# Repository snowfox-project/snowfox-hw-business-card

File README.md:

# Snowfox HW Business Card

## PCB

### Top

### Bottom

## Microcontroller

### pin usage

| pin | signal | direction | comment |
|-----|----------|-------------|--------------|
| gpio_0 | LED | output | user led |
| gpio_1 | GPIO_1 | undefined | |
| gpio_2 | SPI_CS_SD | output | chip select SD card |
| gpio_3 | SPI_MOSI | output | |
| gpio_4 | SPI_MISO | input | |
| gpio_5 | SPI_CLK | output | |
| gpio_9 | SPI_CS_DIS | output | chip selecet display |
| gpio_10 | DIS_RESET# | output | display reset |
| gpio_11 | DIS_D_C# | output | display data/command |
| gpio_12 | I2C_SDA | bidir | I2C data |
| gpio_13 | I2C_SCL | output | I2C clock |
| gpio_16 | RX | input | serial rx to USB |
| gpio_17 | TX | output | serial tx to USB |
| gpio_18 | EXT_TX | output | serial tx to expansion connector |
| gpio_19 | DIS_BUSY | input | display busy |
| gpio_20 | NFC_BUSY | input | nfc busy |
| gpio_21 | BUTTON_A | input | button left |
| gpio_22 | BUTTON_B | input | button right |
| gpio_23 | EXT_RX | input | serial rx to expansion connector |

### i2c addresses

| address | device | comment |
|-----|----------|--------------|
| 0x18 | BMA253 | accelerometer |
| 0x53 | M24LR | NFC eeprom - memory area |
| 0x57 | M24LR | NFC eeprom - security and data area |
| 0x60 | ATECC608A | crypto device |

The M24LR blocks two I2C adresses.

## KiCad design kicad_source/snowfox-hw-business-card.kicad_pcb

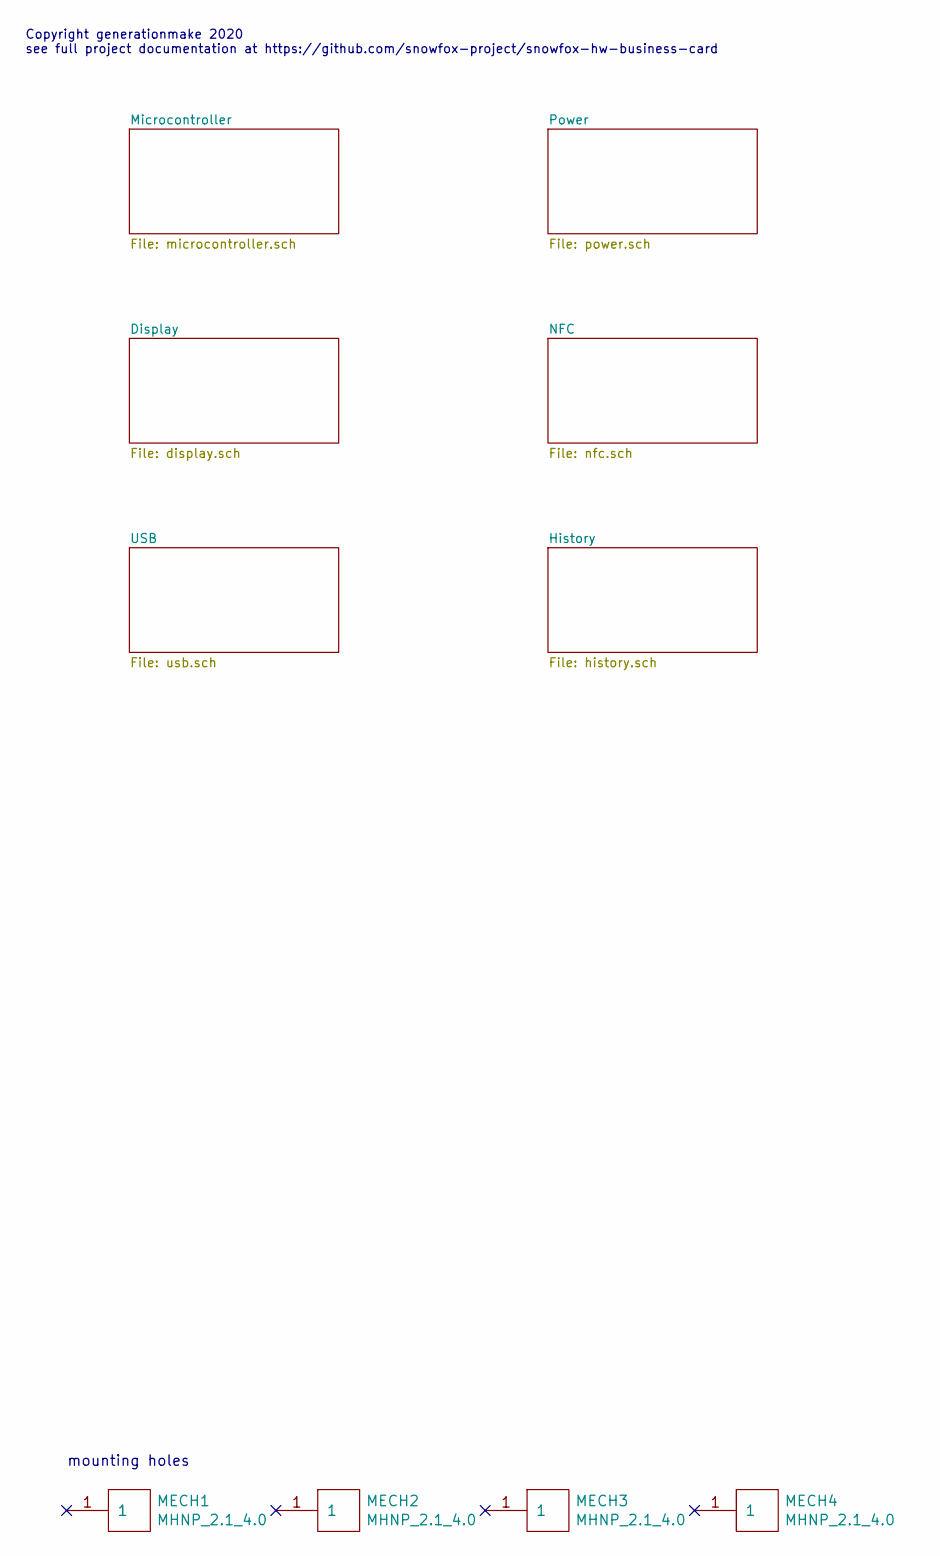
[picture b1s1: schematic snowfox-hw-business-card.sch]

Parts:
MECH1, MECH2, MECH3, MECH4: MHNP_2.1_4.0; MH_210_400_NP

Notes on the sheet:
mounting holes
Copyright generationmake 2020 see full project documentation at https://github.com/snowfox-project/snowfox-hw-business-card

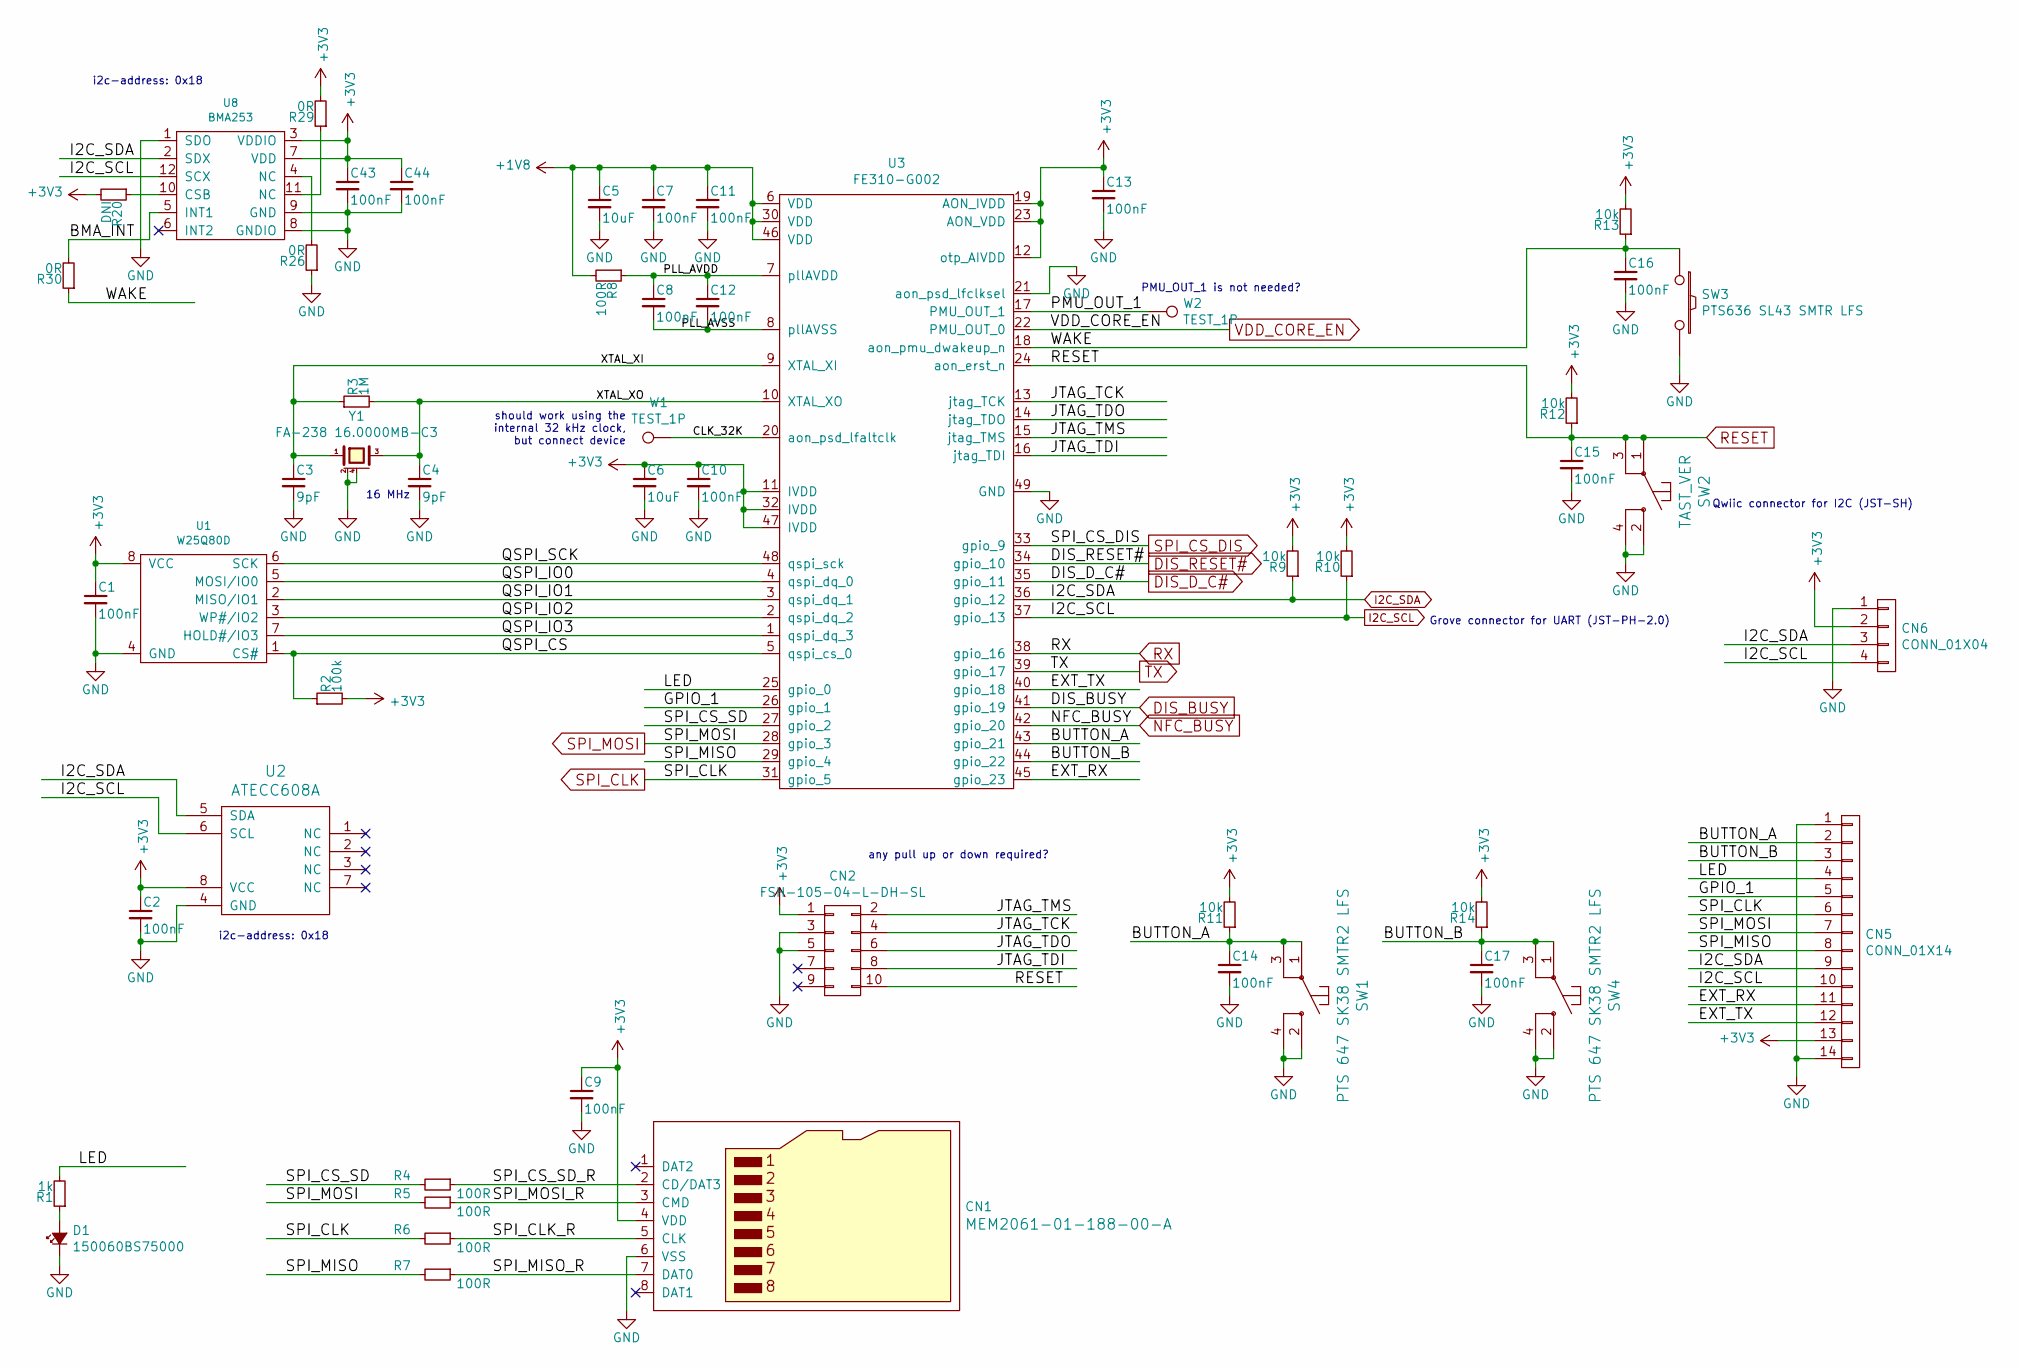
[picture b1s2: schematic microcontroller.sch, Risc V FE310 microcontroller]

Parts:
C1, C2, C7, C8, C9, C10, C11, C12, C13, C14, C15, C16, C17, C43, C44: 100nF; C_0603
C3, C4: 9pF; C_0603
C5, C6: 10uF; C_0603
CN1: MEM2061-01-188-00-A; WE_693071010811
CN2: FSH-105-04-L-DH-SL
CN5: CONN_01X14; SIB-114-02-F-S_MATING
CN6: CONN_01X04; Connectors_JST_SM04B-SRSS-TB
D1: 150060BS75000; LED_0603
R1: 1k; R_0603
R2: 100k; R_0603
R3: 1M; R_0603
R4, R5, R6, R7, R8: 100R; R_0603
R9, R10, R11, R12, R13, R14: 10k; R_0603
R20: DNI; R_0603
R26, R29, R30: 0R; R_0603
SW1, SW4: PTS 647 SK38 SMTR2 LFS; CK_PTS647
SW2: TAST_VER; WE_434351045816
SW3: PTS636 SL43 SMTR LFS; WE_434121050816
U1: W25Q80D; SOIC-8_3.9x4.9mm_Pitch1.27mm
U2: ATECC608A; SOIC-8_3.9x4.9mm_Pitch1.27mm
U3: FE310-G002; QFN-48-1EP_6x6mm_P0.4mm_EP4.3x4.3mm
U8: BMA253; BMA400
W1, W2: TEST_1P; SolderWirePad_single_1mmSMD
Y1: FA-238 16.0000MB-C3; Crystal_SMD_3.2x2.5mm_4Pad

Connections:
+1V8: C5.1, C7.1, C11.1, R8.2, U3.6 (VDD), U3.30 (VDD), U3.46 (VDD); also elsewhere on the board
+3V3: C1.1, C2.1, C6.1, C9.1, C10.1, C13.1, C43.1, C44.1, CN1.4 (VDD), CN2.1, CN5.13, CN6.2, R2.2, R9.2, R10.2, R11.2, R12.2, R13.2, R14.2, R20.2, R29.2, U1.8 (VCC), U2.8 (VCC), U3.11 (IVDD), U3.12 (otp_AIVDD), U3.19 (AON_IVDD), U3.23 (AON_VDD), U3.32 (IVDD), U3.47 (IVDD), U8.3 (VDDIO), U8.7 (VDD); also elsewhere on the board
/Microcontroller/BMA_INT: R30.2, U8.5 (INT1)
/Microcontroller/BUTTON_A: C14.1, CN5.2, R11.1, SW1.1, SW1.3, U3.43 (gpio_21)
/Microcontroller/BUTTON_B: C17.1, CN5.3, R14.1, SW4.1, SW4.3, U3.44 (gpio_22)
/Microcontroller/CLK_32K: U3.20 (aon_psd_lfaltclk), W1.1
/Microcontroller/EXT_RX: CN5.11, U3.45 (gpio_23)
/Microcontroller/EXT_TX: CN5.12, U3.40 (gpio_18)
/Microcontroller/GPIO_1: CN5.5, U3.26 (gpio_1)
/Microcontroller/JTAG_TCK: CN2.4, U3.13 (jtag_TCK)
/Microcontroller/JTAG_TDI: CN2.8, U3.16 (jtag_TDI)
/Microcontroller/JTAG_TDO: CN2.6, U3.14 (jtag_TDO)
/Microcontroller/JTAG_TMS: CN2.2, U3.15 (jtag_TMS)
/Microcontroller/LED: CN5.4, R1.2, U3.25 (gpio_0)
/Microcontroller/PLL_AVDD: C8.1, C12.1, R8.1, U3.7 (pllAVDD)
/Microcontroller/PLL_AVSS: C8.2, C12.2, U3.8 (pllAVSS)
/Microcontroller/PMU_OUT_1: U3.17 (PMU_OUT_1), W2.1
/Microcontroller/QSPI_CS: R2.1, U1.1 (CS#), U3.5 (qspi_cs_0)
/Microcontroller/QSPI_IO0: U1.5 (MOSI/IO0), U3.4 (qspi_dq_0)
/Microcontroller/QSPI_IO1: U1.2 (MISO/IO1), U3.3 (qspi_dq_1)
/Microcontroller/QSPI_IO2: U1.3 (WP#/IO2), U3.2 (qspi_dq_2)
/Microcontroller/QSPI_IO3: U1.7 (HOLD#/IO3), U3.1 (qspi_dq_3)
/Microcontroller/QSPI_SCK: U1.6 (SCK), U3.48 (qspi_sck)
/Microcontroller/SPI_CLK_R: CN1.5 (CLK), R6.1
/Microcontroller/SPI_CS_SD: R4.2, U3.27 (gpio_2)
/Microcontroller/SPI_CS_SD_R: CN1.2 (CD/DAT3), R4.1
/Microcontroller/SPI_MISO: CN5.8, R7.2, U3.29 (gpio_4)
/Microcontroller/SPI_MISO_R: CN1.7 (DAT0), R7.1
/Microcontroller/SPI_MOSI_R: CN1.3 (CMD), R5.1
/Microcontroller/WAKE: C16.1, R13.1, R30.1, SW3.1, U3.18 (aon_pmu_dwakeup_n)
/Microcontroller/XTAL_XI: C3.1, R3.1, U3.9 (XTAL_XI), Y1.1
/Microcontroller/XTAL_XO: C4.1, R3.2, U3.10 (XTAL_XO), Y1.3
DIS_BUSY: U3.41 (gpio_19); also elsewhere on the board
DIS_D_C#: U3.35 (gpio_11); also elsewhere on the board
DIS_RESET#: U3.34 (gpio_10); also elsewhere on the board
GND: C1.2, C2.2, C3.2, C4.2, C5.2, C6.2, C7.2, C9.2, C10.2, C11.2, C13.2, C14.2, C15.2, C16.2, C17.2, C43.2, C44.2, CN1.6 (VSS), CN2.3, CN2.5, CN5.1, CN5.14, CN6.1, D1.1 (K), R26.1, SW1.2, SW1.4, SW2.2, SW2.4, SW3.2, SW4.2, SW4.4, U1.4 (GND), U2.4 (GND), U3.21 (aon_psd_lfclksel), U3.49 (GND), U8.1 (SDO), U8.8 (GNDIO), U8.9 (GND), Y1.2 (case), Y1.4 (case); also elsewhere on the board
I2C_SCL: CN5.10, CN6.4, R10.1, U2.6 (SCL), U3.37 (gpio_13), U8.12 (SCX); also elsewhere on the board
I2C_SDA: CN5.9, CN6.3, R9.1, U2.5 (SDA), U3.36 (gpio_12), U8.2 (SDX); also elsewhere on the board
NFC_BUSY: U3.42 (gpio_20); also elsewhere on the board
unnamed: D1.2 (A), R1.1
unnamed: R20.1, U8.10 (CSB)
unnamed: R26.2, U8.4 (NC)
unnamed: R29.1, U8.11 (NC)
RESET: C15.1, CN2.10, R12.1, SW2.1, SW2.3, U3.24 (aon_erst_n); also elsewhere on the board
RX: U3.38 (gpio_16); also elsewhere on the board
SPI_CLK: CN5.6, R6.2, U3.31 (gpio_5); also elsewhere on the board
SPI_CS_DIS: U3.33 (gpio_9); also elsewhere on the board
SPI_MOSI: CN5.7, R5.2, U3.28 (gpio_3); also elsewhere on the board
TX: U3.39 (gpio_17); also elsewhere on the board
VDD_CORE_EN: U3.22 (PMU_OUT_0); also elsewhere on the board

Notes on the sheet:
should work using the internal 32 kHz clock, but connect device
PMU_OUT_1 is not needed?
any pull up or down required?
Qwiic connector for I2C (JST-SH)
Grove connector for UART (JST-PH-2.0)
16 MHz
i2c-address: 0x18

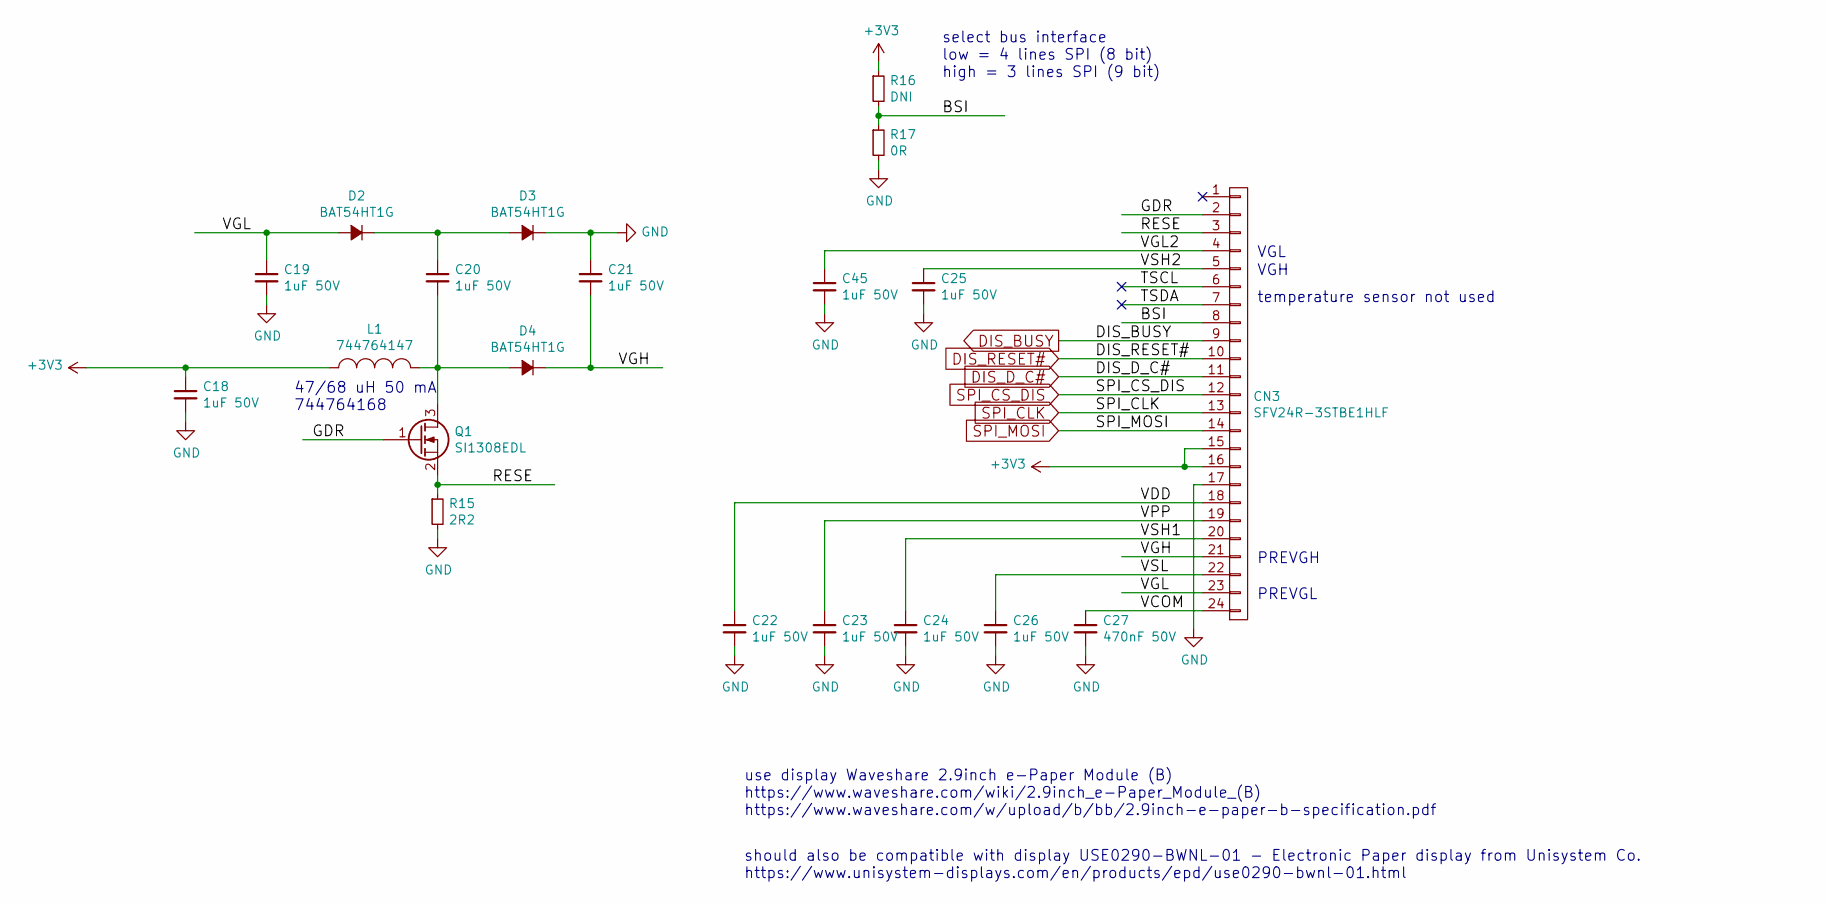
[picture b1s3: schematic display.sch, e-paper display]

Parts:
C18, C19, C20, C21, C22, C23, C24, C25, C26, C45: 1uF 50V; C_0603
C27: 470nF 50V; C_0603
CN3: SFV24R-3STBE1HLF; WR-FPC_68712414522
D2, D3, D4: BAT54HT1G; SOD-323
L1: 744764147; R_1210
Q1: SI1308EDL; SOT-323
R15: 2R2; R_0603
R16: DNI; R_0603
R17: 0R; R_0603

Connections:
+3V3: C18.1, CN3.15, CN3.16, L1.1, R16.1; also elsewhere on the board
/Display/BSI: CN3.8, R16.2, R17.1
/Display/GDR: CN3.2, Q1.1 (G)
/Display/RESE: CN3.3, Q1.2 (S), R15.1
/Display/VCOM: C27.1, CN3.24
/Display/VDD: C22.1, CN3.18
/Display/VGH: C21.2, CN3.21, D4.1 (K)
/Display/VGL: C19.1, CN3.23, D2.2 (A)
/Display/VGL2: C45.1, CN3.4
/Display/VPP: C23.1, CN3.19
/Display/VSH1: C24.1, CN3.20
/Display/VSH2: C25.1, CN3.5
/Display/VSL: C26.1, CN3.22
DIS_BUSY: CN3.9; also elsewhere on the board
DIS_D_C#: CN3.11; also elsewhere on the board
DIS_RESET#: CN3.10; also elsewhere on the board
GND: C18.2, C19.2, C21.1, C22.2, C23.2, C24.2, C25.2, C26.2, C27.2, C45.2, CN3.17, D3.1 (K), R15.2, R17.2; also elsewhere on the board
unnamed: C20.1, D2.1 (K), D3.2 (A)
unnamed: C20.2, D4.2 (A), L1.2, Q1.3 (D)
SPI_CLK: CN3.13; also elsewhere on the board
SPI_CS_DIS: CN3.12; also elsewhere on the board
SPI_MOSI: CN3.14; also elsewhere on the board

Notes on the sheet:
temperature sensor not used
select bus interface low = 4 lines SPI (8 bit) high = 3 lines SPI (9 bit)
use display Waveshare 2.9inch e-Paper Module (B) https://www.waveshare.com/wiki/2.9inch_e-Paper_Module_(B) https://www.waveshare.com/w/upload/b/bb/2.9inch-e-paper-b-specification.pdf
47/68 uH 50 mA 744764168
should also be compatible with display USE0290-BWNL-01 - Electronic Paper display from Unisystem Co. https://www.unisystem-displays.com/en/products/epd/use0290-bwnl-01.html
VGL
VGH
PREVGH
PREVGL

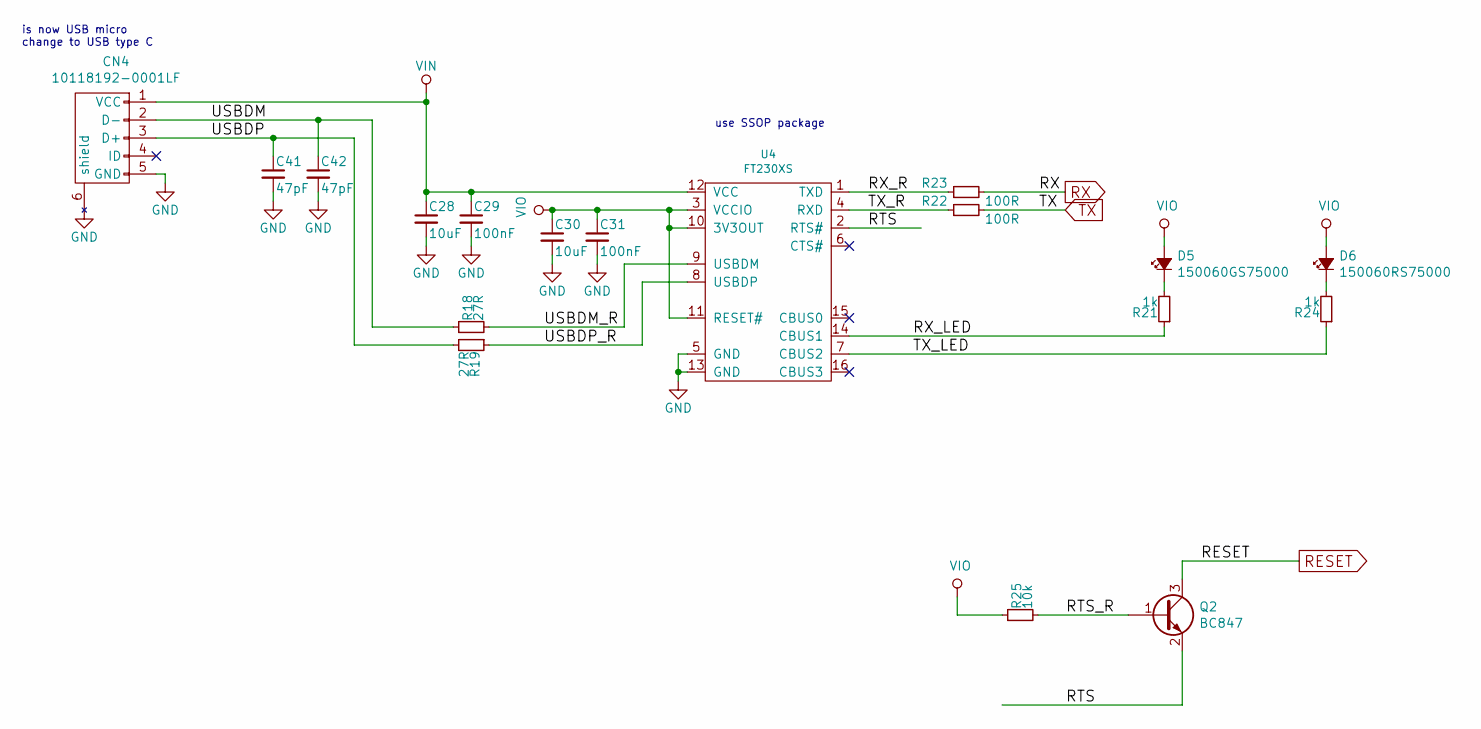
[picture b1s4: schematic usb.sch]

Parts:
C28, C30: 10uF; C_0603
C29, C31: 100nF; C_0603
C41, C42: 47pF; C_0603
CN4: 10118192-0001LF; 10118192-000xLF
D5: 150060GS75000; LED_0603
D6: 150060RS75000; LED_0603
Q2: BC847; SOT-23
R18, R19: 27R; R_0603
R21, R24: 1k; R_0603
R22, R23: 100R; R_0603
R25: 10k; R_0603
U4: FT230XS; SSOP-16_3.9x4.9mm_Pitch0.635mm

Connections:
/USB/RTS: Q2.2 (E), U4.2 (RTS#)
/USB/RTS_R: Q2.1 (B), R25.2
/USB/RX_LED: R21.1, U4.14 (CBUS1)
/USB/RX_R: R23.1, U4.1 (TXD)
/USB/TX_LED: R24.1, U4.7 (CBUS2)
/USB/TX_R: R22.1, U4.4 (RXD)
/USB/USBDM: C42.1, CN4.2 (D-), R18.1
/USB/USBDM_R: R18.2, U4.9 (USBDM)
/USB/USBDP: C41.1, CN4.3 (D+), R19.2
/USB/USBDP_R: R19.1, U4.8 (USBDP)
GND: C28.2, C29.2, C30.2, C31.2, C41.2, C42.2, CN4.5 (GND), CN4.6 (shield), U4.5 (GND), U4.13 (GND); also elsewhere on the board
unnamed: D5.1 (K), R21.2
unnamed: D6.1 (K), R24.2
RESET: Q2.3 (C); also elsewhere on the board
RX: R23.2; also elsewhere on the board
TX: R22.2; also elsewhere on the board
VIN: C28.1, C29.1, CN4.1 (VCC), U4.12 (VCC); also elsewhere on the board
VIO: C30.1, C31.1, D5.2 (A), D6.2 (A), R25.1, U4.3 (VCCIO), U4.10 (3V3OUT), U4.11 (RESET#)

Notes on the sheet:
is now USB micro change to USB type C
use SSOP package

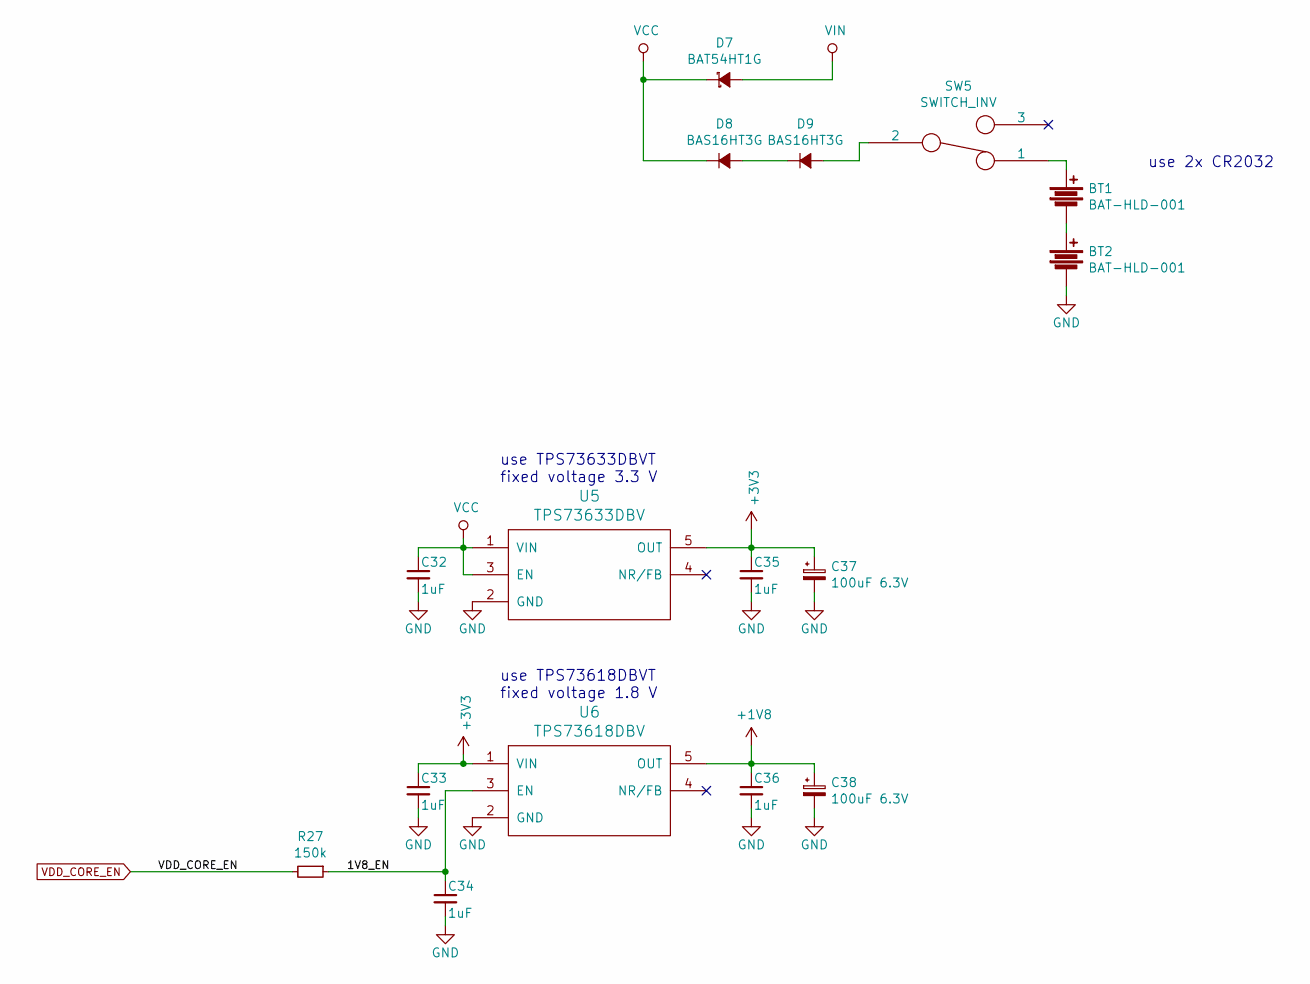
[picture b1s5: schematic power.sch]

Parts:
BT1, BT2: BAT-HLD-001; Wuerth_WA-BCMC_79523141
C32, C33, C34, C35, C36: 1uF; C_0603
C37, C38: 100uF 6.3V; TantalC_SizeD_EIA-7343_Reflow
D7: BAT54HT1G; SOD-323
D8, D9: BAS16HT3G; SOD-323
R27: 150k; R_0603
SW5: SWITCH_INV; WE_450404015514
U5: TPS73633DBV; SOT-23-5
U6: TPS73618DBV; SOT-23-5

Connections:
+1V8: C36.1, C38.1, U6.5 (OUT); also elsewhere on the board
+3V3: C33.1, C35.1, C37.1, U5.5 (OUT), U6.1 (VIN); also elsewhere on the board
/Power/1V8_EN: C34.1, R27.1, U6.3 (EN)
GND: BT2.2, C32.2, C33.2, C34.2, C35.2, C36.2, C37.2, C38.2, U5.2 (GND), U6.2 (GND); also elsewhere on the board
unnamed: BT1.1, SW5.1
unnamed: BT1.2, BT2.1
unnamed: D8.2 (A), D9.1 (K)
unnamed: D9.2 (A), SW5.2
VCC: C32.1, D7.1 (K), D8.1 (K), U5.1 (VIN), U5.3 (EN)
VDD_CORE_EN: R27.2; also elsewhere on the board
VIN: D7.2 (A); also elsewhere on the board

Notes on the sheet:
use TPS73633DBVT fixed voltage 3.3 V
use TPS73618DBVT fixed voltage 1.8 V
use 2x CR2032

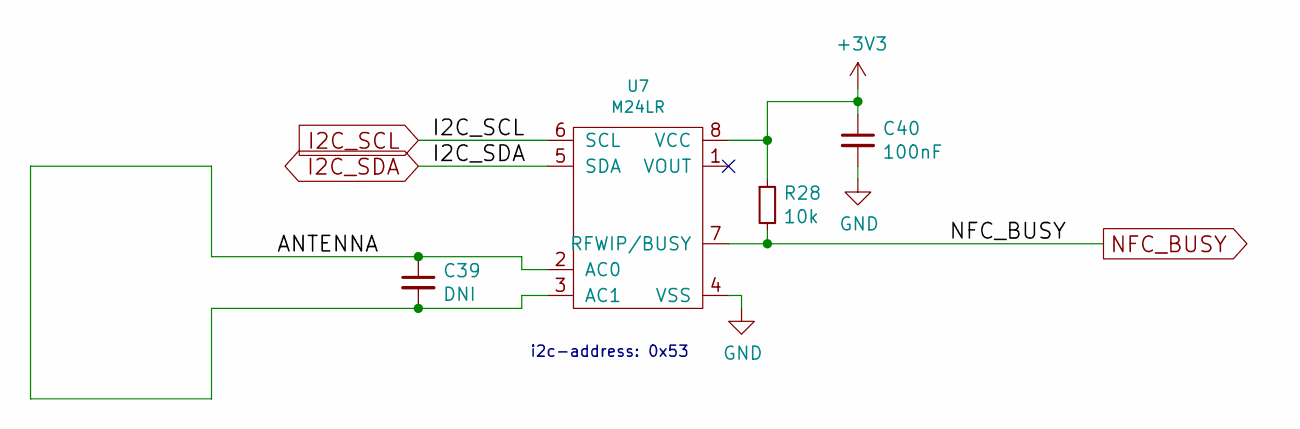
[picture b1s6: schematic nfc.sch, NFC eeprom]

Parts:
C39: DNI; C_0603
C40: 100nF; C_0603
R28: 10k; R_0603
U7: M24LR; SOIC-8_3.9x4.9mm_Pitch1.27mm

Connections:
+3V3: C40.1, R28.1, U7.8 (VCC); also elsewhere on the board
/NFC/ANTENNA: C39.1, C39.2, U7.2 (AC0), U7.3 (AC1)
GND: C40.2, U7.4 (VSS); also elsewhere on the board
I2C_SCL: U7.6 (SCL); also elsewhere on the board
I2C_SDA: U7.5 (SDA); also elsewhere on the board
NFC_BUSY: R28.2, U7.7 (RFWIP/BUSY); also elsewhere on the board

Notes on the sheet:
i2c-address: 0x53

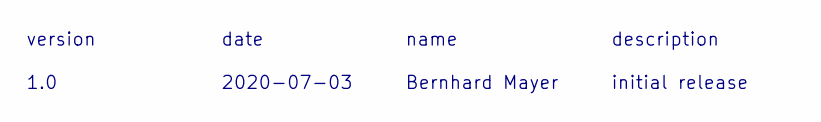
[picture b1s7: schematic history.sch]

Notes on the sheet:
version
date
name
description
1.0
2020-07-03
Bernhard Mayer
initial release

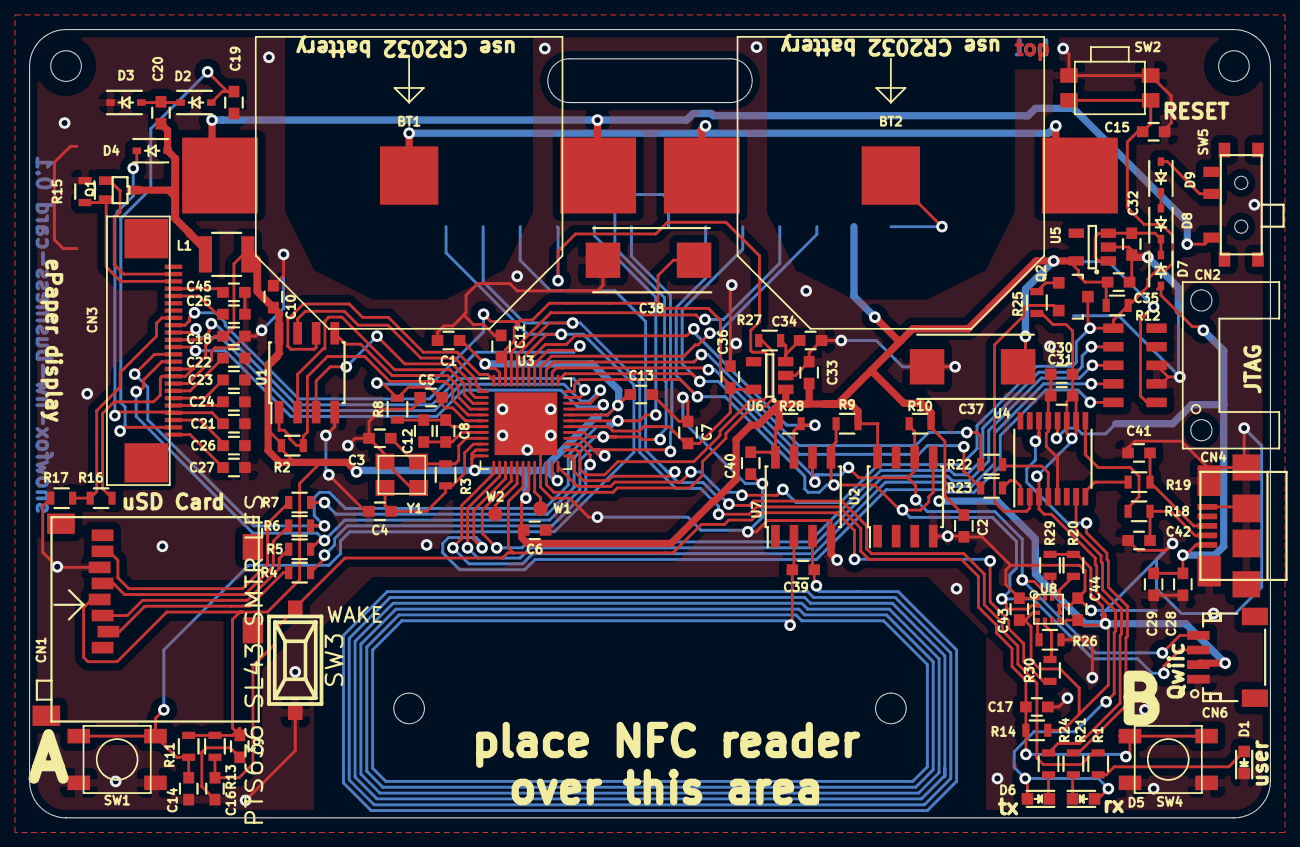
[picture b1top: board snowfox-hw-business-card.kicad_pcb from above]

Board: 2 copper layers, 85.0 x 54.0 mm, 115 parts (1 on the bottom side), 85 nets.

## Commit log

2020-05-02 added README
2020-05-06 added files for project
2020-05-07 added some schematic pages from other projects
2020-05-09 placed FE310, made first connections
2020-05-09 updated power circuit
2020-05-10 added flash, JTAG connector and display to schematic
2020-05-10 added nfc part, generated schematic pdf
2020-05-11 started placement
2020-05-12 made first placement
2020-05-12 added renderings of pcb
2020-05-12 added value 16 MHz to crystal, connected pin 1 of CN2 to +3V3
2020-05-12 changed connector for display
2020-05-14 changed usb controller to FTDI FT230XS
2020-05-14 added qwiic connector for I2C and grove connector for UART
2020-05-14 updated schematic pdf and renderings
2020-05-15 added BMA400 accelerometer
2020-05-15 added rendering of business card with display
2020-05-19 changed JTAG connector
2020-06-02 used small side switch for reset, added expansion connector,changed mounting holes
2020-06-02 updated pdf schematic
2020-06-02 updated screenshots
2020-06-02 changed to smaller crystal footprint
2020-06-02 routed some traces
2020-06-07 changed diodes to smaller footprint, connected all lines in layout, updated images
2020-06-07 made pcb edges round, added slot for mounting
2020-06-07 rearranged parts for display
2020-06-07 reworked silk screen
2020-06-10 changed wake button to smaller type, moved button A to left side, made some layout
2020-06-12 corrected some part numbers
2020-06-14 added some missing part numbers
2020-06-14 changed BMA400 to BMA253, changed SD-Card-Socket to MEM2061-01-188-00-A and changed battery holder to BAT-HLD-001 for cost reduction
2020-06-15 optimized parts for BOM costs
2020-06-15 connected interrupt line of BMA253, updated layout
2020-06-18 added test points, finished layout
2020-06-18 added pdf schematic
2020-06-18 updated images
2020-07-02 exchanged rx and tx of usb serial
2020-07-03 reworked reset circuit at usb serial
2020-07-03 added C45 to pin4 of display
2020-07-03 updated silk screen, added labels, added qrcode
2020-07-03 updated images of pcb
2020-07-04 added snowfox logo
2020-07-09 added pdfs of layout
2020-07-09 added step file
2020-07-09 added freecad files of complete business card, updated images
2020-07-09 added pin description to readme
2020-07-09 added i2c addresses to schematic pdf and readme
2020-07-22 started display support frame
2020-07-23 updated display frame, updated renderings
2020-07-26 added missing parts to 3d model, updated step file
2020-07-26 added production data for display frame
2020-08-15 Updated information on I2C of M24LR
2020-08-16 reworked display holder, increased some clearances, added hole for Qwiic connector
2020-08-18 Adding minimal firmware for blinking the LED of the FE310
2020-08-18 Adding minimal README
